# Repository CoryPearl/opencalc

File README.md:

<p align="center"><strong>Prototype sponsored by <a href="https://www.pcbway.com/">PCBWay</a>.</strong></p>

OpenCalc is an open-source graphing calculator inspired by the TI-84, built around an ESP32-S3, a color LCD, USB-C, Python-style scripting, games, and expandable firmware.

OpenCalc-authored software is licensed under **GPL-3.0-or-later**. Bundled components retain their original licenses; see [Third-Party Notices](THIRD_PARTY_NOTICES.md).

The calculator runs **OpenCalc OS**, the project’s open-source ESP32-S3 operating environment. OpenCalc OS includes the calculator interface, math and graphing engines, built-in apps, scripting runtime, USB file storage, keypad handling, display drivers, game support, and power management.

Website: [https://corypearl.github.io/opencalc/product-website/](https://corypearl.github.io/opencalc/product-website/)

Blog: [https://corypearl.github.io/opencalc/blog.html](https://corypearl.github.io/opencalc/blog.html)

<p align="center">

</p>
<p align="center"><small>Click an image to enlarge. The UI tour visits all 12 apps and the game menu.</small></p>

## Highlights

- **A real graphing calculator:** textbook-style input, exact and numerical
  math, complex numbers, calculus, history, typed persistent variables, and
  unit-aware expressions such as `8 m / 2 s`.
- **Integrated CAS and graphing:** Giac/KhiCAS symbolic math linked to Cartesian,
  parametric, polar, and sequence graphs, tables, roots, derivatives, tangents,
  integrals, and points of interest. `Alpha` + `Graph` opens exact symbolic
  analysis for the selected graph, including its derivative, integral, roots,
  asymptotes, tangent line, and integral shading. CAS results have selectable
  solution branches, exact/decimal views, domain controls, assumptions, and a
  searchable command catalog.
  All graph modes support per-series colors/styles, mode-aware trace and tables,
  scalable image backgrounds, and direct or recurrent sequences.
- **A complete math toolkit:** Statistics, Lists, Matrices, Solver, Finance,
  Conics, Inequalities, and a searchable science and engineering reference.
- **Reference Center:** press `Alpha` + `Zoom` for an interactive periodic table
  and browsable math, physics, and engineering formulas and explanations.
- **Programmable on the device:** edit, run, upload, and debug Tiny Python programs with
  math, statistics, exceptions, local modules, cancellable forever loops, CAS
  access, graphics, storage, audio, and protected CircuitPython-style sensor objects.
- **[Built for science and electronics](guied.MD#scientific-data-logging):** use Tiny Python,
  12 bidirectional digital pins, four 16-bit analog inputs, and shared I2C to
  control experiments, plot live sensor data, and analyze recordings in Stats.
- **Games included:** press `Alpha` + `2nd` for Tetris, Doom, Snake, Breakout, and NES/Mario support with
  persistent high scores, multi-key controls, and optional audio.
- **Open hardware:** ESP32-S3, 320x240 color display, diode-isolated keypad,
  rechargeable battery, USB-C, expandable storage, and a documented V5 PCB.
- **One-cable workflow:** the same USB-C connection handles charging, firmware
  flashing, serial monitoring, and file storage.
- **Dual-core OpenCalc OS:** one core keeps the interface and graphics responsive
  while the other handles background math and system work, with persistent
  worksheets, configurable performance, and power-saving controls.

## Rough production Cost Estimate

| Cost area                           | Estimate per unit |
| ----------------------------------- | ----------------- |
| PCB electronics parts from BOM      | $11-$16           |
| 320x240 LCD                         | $5                |
| 3.7 V 2000 mAh Li-ion battery       | $3-$5             |
| Cheap keycaps / keypad plastics     | $2-$4             |
| 3d printed case                     | $3-$6             |
| PCB fabrication + SMT assembly      | $5-$9             |
| Bulk shipping / logistics allowance | $3-$6             |
| Estimated production cost           | $32-$51           |

## Project Layout

```text
firmware/   OpenCalc OS source for the ESP32-S3 calculator
hardware/   key layouts, graphics, PCB files, case files, and hardware docs
docs/       notes and project website files
```

## Quick Start

Install and activate ESP-IDF first; see Espressif's
[ESP32-S3 Get Started guide](https://docs.espressif.com/projects/esp-idf/en/latest/esp32s3/get-started/).
Then connect OpenCalc with a data-capable USB-C cable and build the firmware:

```console
cd firmware
idf.py build
```

Find the serial port created by OpenCalc:

| System  | Terminal       | Command                                        |
| ------- | -------------- | ---------------------------------------------- |
| macOS   | Terminal       | `ls /dev/cu.*`                                 |
| Linux   | Terminal       | `ls /dev/ttyACM* /dev/ttyUSB* 2>/dev/null`     |
| Windows | PowerShell     | `[System.IO.Ports.SerialPort]::GetPortNames()` |
| Windows | Command Prompt | `mode`                                         |

Look for a new USB serial device after connecting the calculator. Typical names
are `/dev/cu.usbmodemopencalc1` on macOS, `/dev/ttyACM0` on Linux, or `COM5` on
Windows. Replace `PORT` below with that complete name; do not type the word
`PORT` literally.

If automatic flashing does not enter the bootloader, hold **Boot**, tap
**Reset**, and then release **Boot**. Flash using the detected port:

```text
idf.py -p PORT flash
```

After OpenCalc restarts, find the port again because its name can change between
bootloader and normal operation. Start the serial monitor with the runtime port:

```text
idf.py -p PORT monitor
```

Press `Ctrl+]` to exit the monitor. The same USB-C cable supports flashing,
serial monitoring, storage, and charging.

## Documentation

- [Complete OpenCalc OS Guide](guied.MD): in-depth controls, app workflows, games, scripting, settings, build instructions, validation, and troubleshooting.
- [Tiny Python Start Guide](TINY_PYTHON_START_GUIDE.md): create, run, and debug scripts; use imports, math, files, graphics, audio, keys, and scientific I/O.
- [Firmware README](firmware/FIRMWARE_README.md): build settings, flashing, storage image, controls, apps, games, and firmware status.
- [App Status](firmware/APP_STATUS.md): implementation status for every OpenCalc OS app and game.
- [PCB README](hardware/pcb/PCB_README.md): current V5 PCB parts, pin map, power path, display, keypad, battery, audio, and bring-up checks.
- [Tiny Python README](firmware/main/components/tiny-python-readme.md): scripting runtime details.
- [Tiny Python capability audit](firmware/TINY_PYTHON_AUDIT.md): supported Python and hardware APIs, limits, and the CircuitPython compatibility boundary.

## Current Status

OpenCalc OS is a capable working prototype. Every built-in app has its main
workflow in place, and the calculator, graphing, CAS, scripting, USB storage,
power controls, and all five games are usable. The remaining work is mostly
deeper edge-case handling, long-session reliability, and validation of the new
V5-only hardware features.

| Area | Current estimate |
| --- | ---: |
| Primary app workflows implemented | 12/12 (100%) |
| Automated host test groups passing | 19/19 (100%) |
| Planned software feature coverage | About 87% |
| Everyday workflow usability | About 83% |
| Software reliability confidence | About 75% |
| Production-release readiness | About 50% |

These percentages are practical estimates, not test-coverage measurements. The
biggest jobs left are closing Tiny Python's compatibility gaps, handling very
large CAS results and unusual math edge cases, stress-testing large matrices and
long sessions, and validating V5 audio and scientific I/O on real hardware. See the
[app-by-app status](firmware/APP_STATUS.md) for more detail.

## Credits

- OpenCalc OS, hardware, and enclosure design: [Cory Pearl](https://github.com/CoryPearl).
- CAS engines: [Giac/Xcas](https://xcas.univ-grenoble-alpes.fr/) by Bernard Parisse and contributors, with the [KhiCAS](https://github.com/KhiCAS) ESP32 port lineage under GPL-3.0-or-later; [Eigenmath](https://github.com/georgeweigt/eigenmath) remains as a BSD-2-Clause fallback.
- Doom engine: id Software's GPL Doom source, Simon Howard's Chocolate Doom work, and [doomgeneric](https://github.com/ozkl/doomgeneric) by ozkl, under GPL-2.0-or-later notices.
- NES emulation: [Anemoia-ESP32](https://github.com/Shim06/Anemoia-ESP32) by Shim06 and contributors, under GPLv3.
- Platform: [Espressif ESP-IDF](https://github.com/espressif/esp-idf), TinyUSB, and the ESP LCD ILI9341/ST7789 panel drivers under their respective licenses.
- Prototype project funding was provided in part by [PCBWay](https://pcbway.com).

Complete copyright, license, and game-data details are recorded in [THIRD_PARTY_NOTICES.md](THIRD_PARTY_NOTICES.md). Doom WADs and NES ROMs are separate game data and are not licensed under the OpenCalc firmware license.

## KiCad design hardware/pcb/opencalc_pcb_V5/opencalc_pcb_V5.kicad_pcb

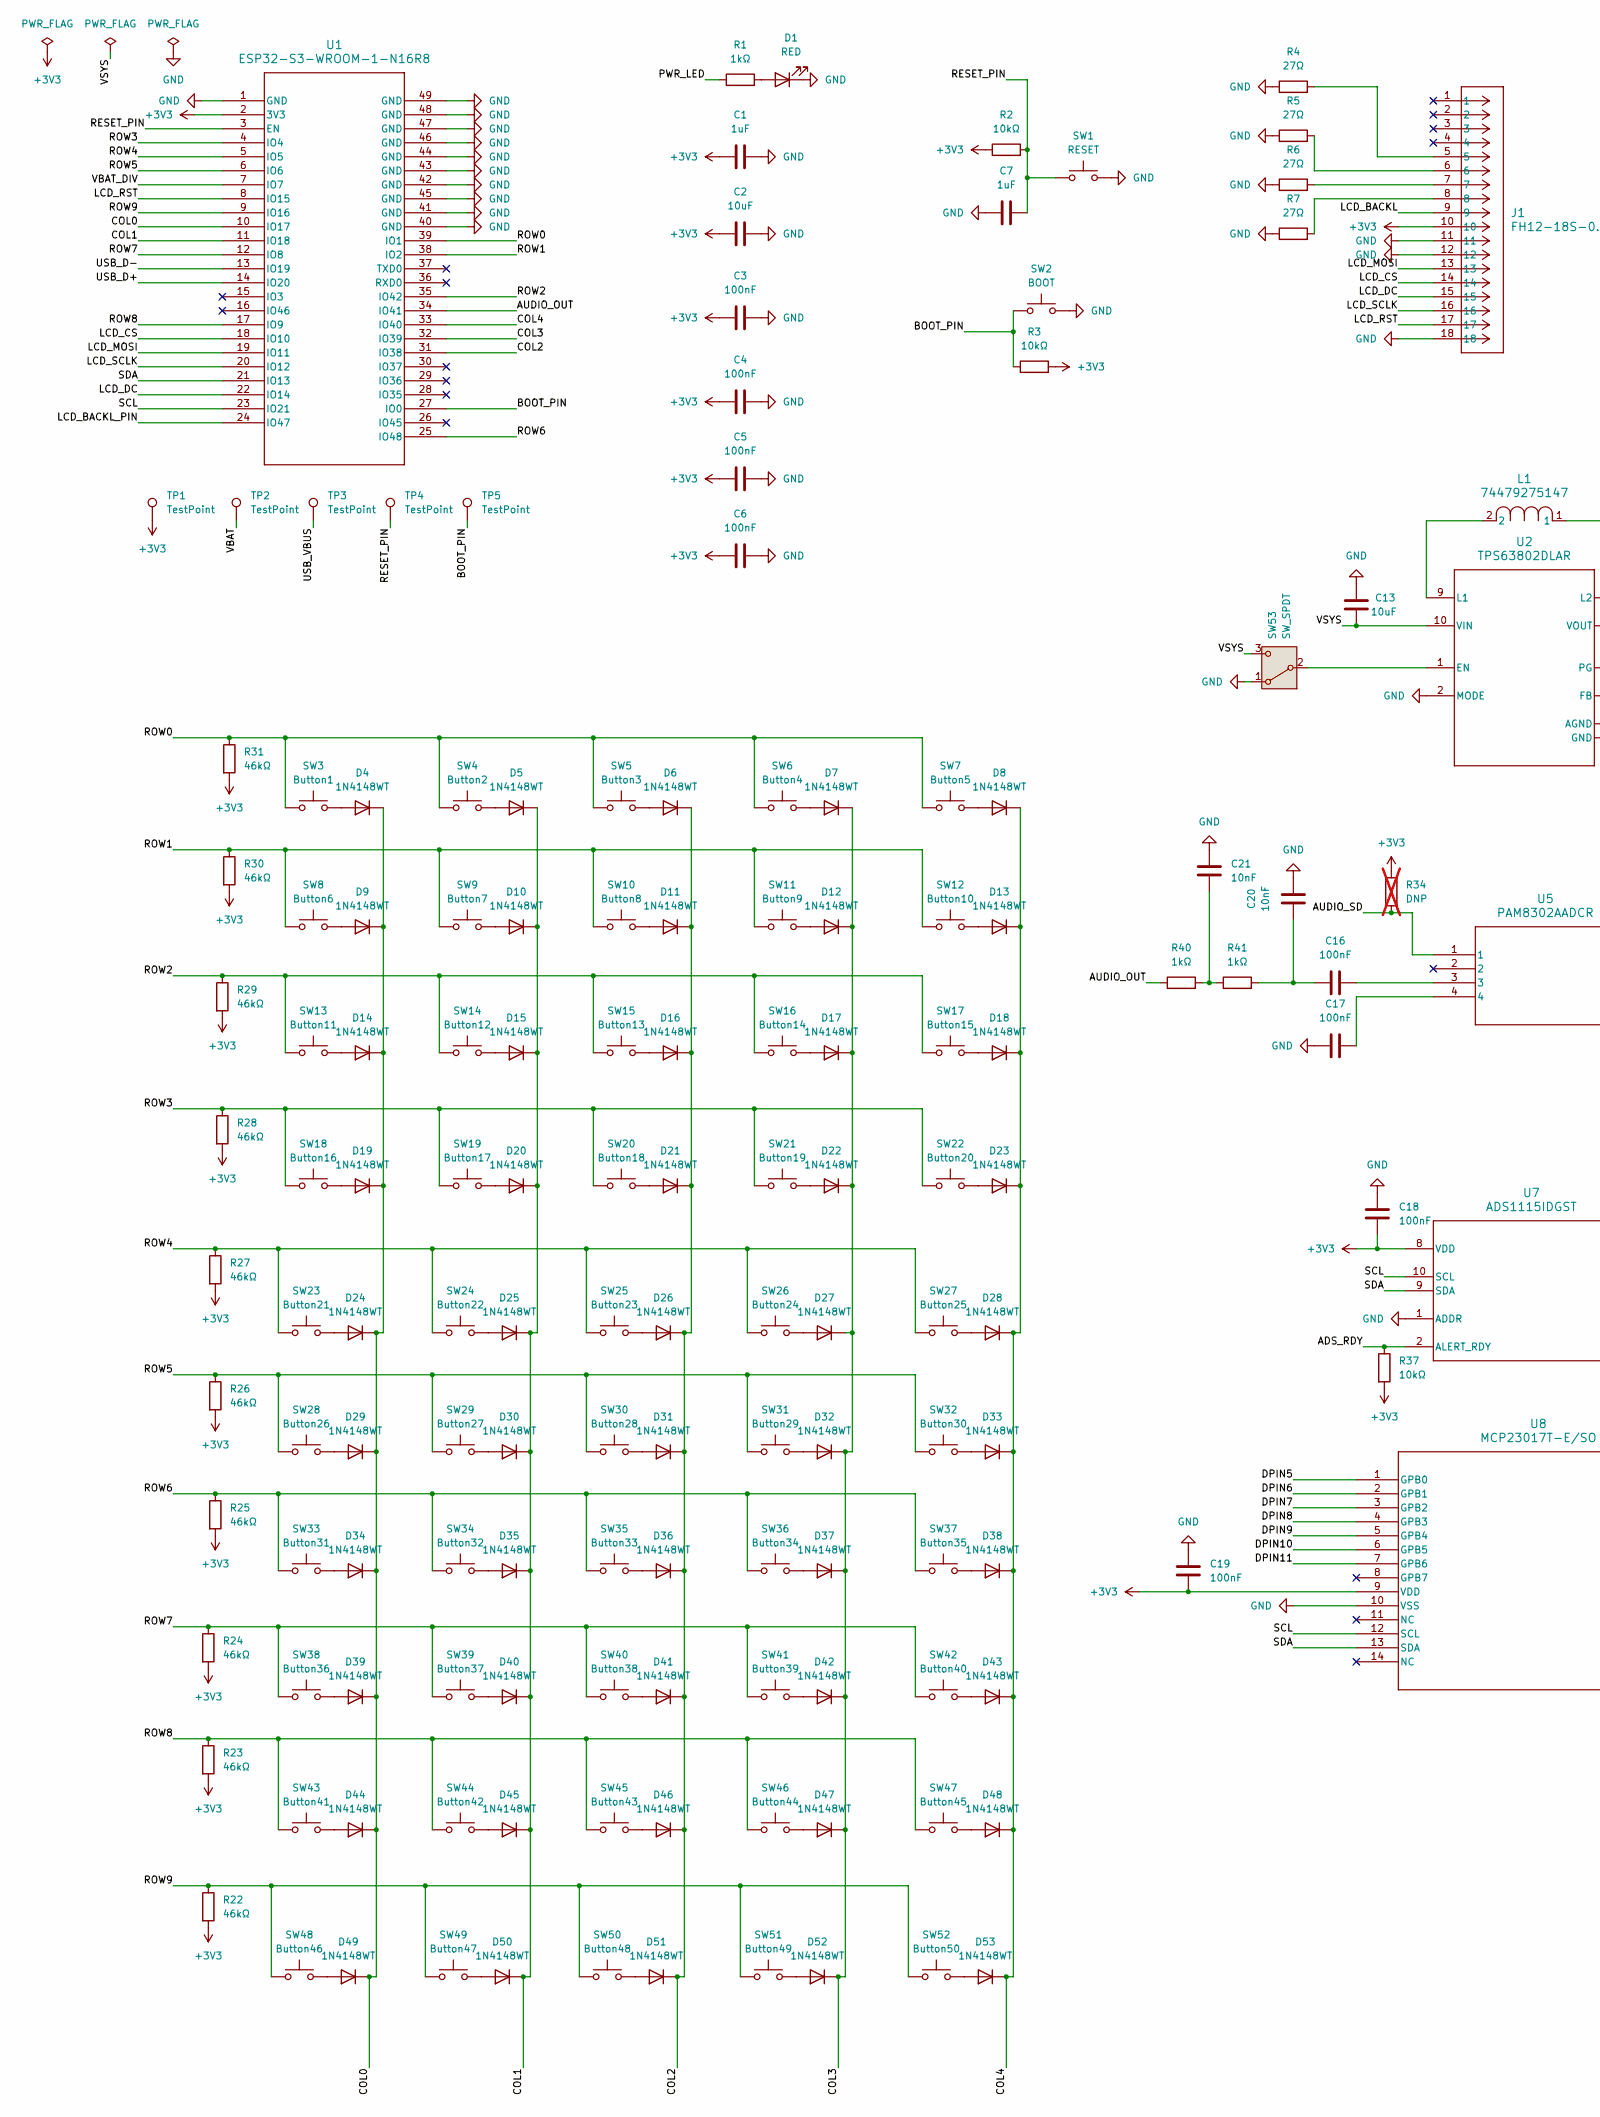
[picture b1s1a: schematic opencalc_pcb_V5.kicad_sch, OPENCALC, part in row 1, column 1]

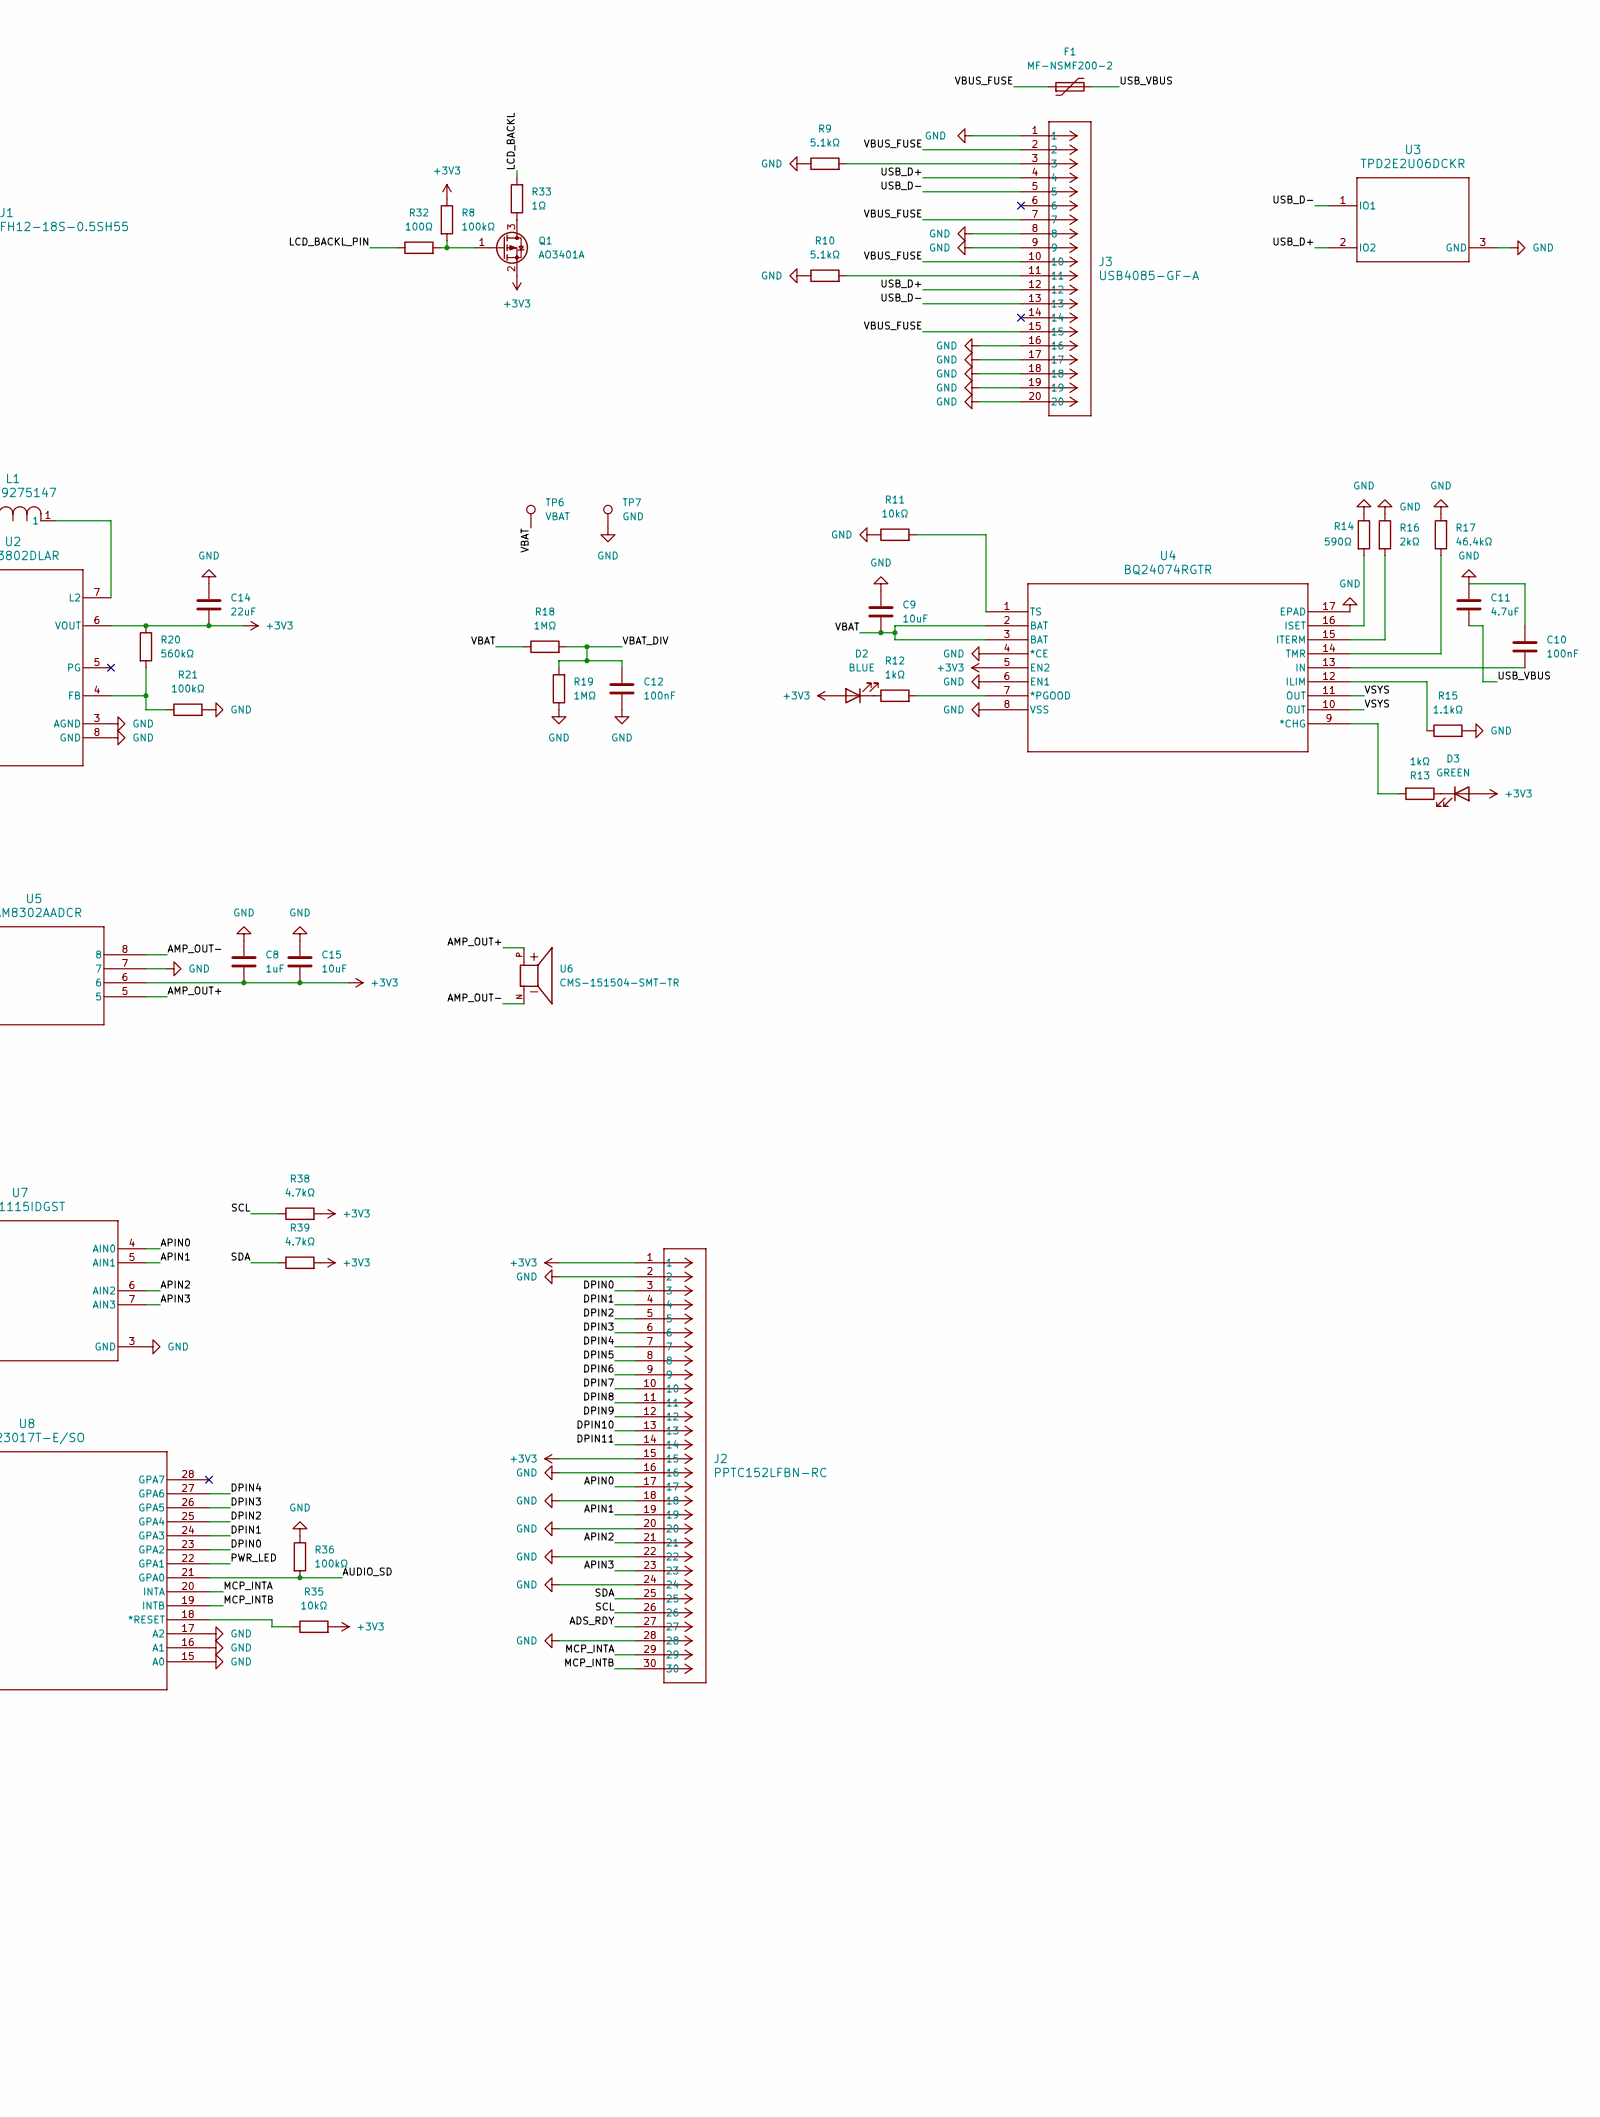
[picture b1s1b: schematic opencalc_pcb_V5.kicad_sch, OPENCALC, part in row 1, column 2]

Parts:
C1, C7, C8: 1uF; C_0805_2012Metric_Pad1.18x1.45mm_HandSolder
C2, C9, C13, C15: 10uF; C_0805_2012Metric_Pad1.18x1.45mm_HandSolder
C3, C4, C5, C6, C10, C12, C16, C17, C18, C19: 100nF; C_0805_2012Metric_Pad1.18x1.45mm_HandSolder
C11: 4.7uF; C_0805_2012Metric_Pad1.18x1.45mm_HandSolder
C14: 22uF; C_0805_2012Metric_Pad1.18x1.45mm_HandSolder
C20, C21: 10nF; C_0805_2012Metric_Pad1.18x1.45mm_HandSolder
D1: RED; LED_0805_2012Metric_Pad1.15x1.40mm_HandSolder
D2: BLUE; LED_0805_2012Metric_Pad1.15x1.40mm_HandSolder
D3: GREEN; LED_0805_2012Metric_Pad1.15x1.40mm_HandSolder
D4, D5, D6, D7, D8, D9, D10, D11, D12, D13, D14, D15, D16, D17, D18, D19, D20, D21, D22, D23, D24, D25, D26, D27, D28, D29, D30, D31, D32, D33, D34, D35, D36, D37, D38, D39, D40, D41, D42, D43, D44, D45, D46, D47, D48, D49, D50, D51, D52, D53: 1N4148WT; D_0805_2012Metric_Pad1.15x1.40mm_HandSolder
F1: MF-NSMF200-2; Fuse_1206_3216Metric
J1: FH12-18S-0.5SH55; FH12-18S-0.5SH(55)
J2: PPTC152LFBN-RC; PPTC152LFBN_RC
J3: USB4085-GF-A
L1: 74479275147
Q1: AO3401A; SOT-23
R1, R12, R13, R40, R41: 1kΩ; R_0805_2012Metric_Pad1.20x1.40mm_HandSolder
R2, R3, R11, R35, R37: 10kΩ; R_0805_2012Metric_Pad1.20x1.40mm_HandSolder
R4, R5, R6, R7: 27Ω; R_0805_2012Metric_Pad1.20x1.40mm_HandSolder
R8, R21, R36: 100kΩ; R_0805_2012Metric_Pad1.20x1.40mm_HandSolder
R9, R10: 5.1kΩ; R_0805_2012Metric_Pad1.20x1.40mm_HandSolder
R14: 590Ω; R_0805_2012Metric_Pad1.20x1.40mm_HandSolder
R15: 1.1kΩ; R_0805_2012Metric_Pad1.20x1.40mm_HandSolder
R16: 2kΩ; R_0805_2012Metric_Pad1.20x1.40mm_HandSolder
R17: 46.4kΩ; R_0805_2012Metric_Pad1.20x1.40mm_HandSolder
R18, R19: 1MΩ; R_0805_2012Metric_Pad1.20x1.40mm_HandSolder
R20: 560kΩ; R_0805_2012Metric_Pad1.20x1.40mm_HandSolder
R22, R23, R24, R25, R26, R27, R28, R29, R30, R31: 46kΩ; R_0805_2012Metric_Pad1.20x1.40mm_HandSolder
R32: 100Ω; R_0805_2012Metric_Pad1.20x1.40mm_HandSolder
R33: 1Ω; R_0805_2012Metric_Pad1.20x1.40mm_HandSolder
R34: DNP; R_0805_2012Metric_Pad1.20x1.40mm_HandSolder; not fitted
R38, R39: 4.7kΩ; R_0805_2012Metric_Pad1.20x1.40mm_HandSolder
SW1: RESET; SW_Push_1P1T_NO_E-Switch_TL3301NxxxxxG
SW2: BOOT; SW_Push_1P1T_NO_E-Switch_TL3301NxxxxxG
SW3: Button1; SW_Push_1P1T_NO_E-Switch_TL3301NxxxxxG
SW4: Button2; SW_Push_1P1T_NO_E-Switch_TL3301NxxxxxG
SW5: Button3; SW_Push_1P1T_NO_E-Switch_TL3301NxxxxxG
SW6: Button4; SW_Push_1P1T_NO_E-Switch_TL3301NxxxxxG
SW7: Button5; SW_Push_1P1T_NO_E-Switch_TL3301NxxxxxG
SW8: Button6; SW_Push_1P1T_NO_E-Switch_TL3301NxxxxxG
SW9: Button7; SW_Push_1P1T_NO_E-Switch_TL3301NxxxxxG
SW10: Button8; SW_Push_1P1T_NO_E-Switch_TL3301NxxxxxG
SW11: Button9; SW_Push_1P1T_NO_E-Switch_TL3301NxxxxxG
SW12: Button10; SW_Push_1P1T_NO_E-Switch_TL3301NxxxxxG
SW13: Button11; SW_Push_1P1T_NO_E-Switch_TL3301NxxxxxG
SW14: Button12; SW_Push_1P1T_NO_E-Switch_TL3301NxxxxxG
SW15: Button13; SW_Push_1P1T_NO_E-Switch_TL3301NxxxxxG
SW16: Button14; SW_Push_1P1T_NO_E-Switch_TL3301NxxxxxG
SW17: Button15; SW_Push_1P1T_NO_E-Switch_TL3301NxxxxxG
SW18: Button16; SW_Push_1P1T_NO_E-Switch_TL3301NxxxxxG
SW19: Button17; SW_Push_1P1T_NO_E-Switch_TL3301NxxxxxG
SW20: Button18; SW_Push_1P1T_NO_E-Switch_TL3301NxxxxxG
SW21: Button19; SW_Push_1P1T_NO_E-Switch_TL3301NxxxxxG
SW22: Button20; SW_Push_1P1T_NO_E-Switch_TL3301NxxxxxG
SW23: Button21; SW_Push_1P1T_NO_E-Switch_TL3301NxxxxxG
SW24: Button22; SW_Push_1P1T_NO_E-Switch_TL3301NxxxxxG
SW25: Button23; SW_Push_1P1T_NO_E-Switch_TL3301NxxxxxG
SW26: Button24; SW_Push_1P1T_NO_E-Switch_TL3301NxxxxxG
SW27: Button25; SW_Push_1P1T_NO_E-Switch_TL3301NxxxxxG
SW28: Button26; SW_Push_1P1T_NO_E-Switch_TL3301NxxxxxG
SW29: Button27; SW_Push_1P1T_NO_E-Switch_TL3301NxxxxxG
SW30: Button28; SW_Push_1P1T_NO_E-Switch_TL3301NxxxxxG
SW31: Button29; SW_Push_1P1T_NO_E-Switch_TL3301NxxxxxG
SW32: Button30; SW_Push_1P1T_NO_E-Switch_TL3301NxxxxxG
SW33: Button31; SW_Push_1P1T_NO_E-Switch_TL3301NxxxxxG
SW34: Button32; SW_Push_1P1T_NO_E-Switch_TL3301NxxxxxG
SW35: Button33; SW_Push_1P1T_NO_E-Switch_TL3301NxxxxxG
SW36: Button34; SW_Push_1P1T_NO_E-Switch_TL3301NxxxxxG
SW37: Button35; SW_Push_1P1T_NO_E-Switch_TL3301NxxxxxG
SW38: Button36; SW_Push_1P1T_NO_E-Switch_TL3301NxxxxxG
SW39: Button37; SW_Push_1P1T_NO_E-Switch_TL3301NxxxxxG
SW40: Button38; SW_Push_1P1T_NO_E-Switch_TL3301NxxxxxG
SW41: Button39; SW_Push_1P1T_NO_E-Switch_TL3301NxxxxxG
SW42: Button40; SW_Push_1P1T_NO_E-Switch_TL3301NxxxxxG
SW43: Button41; SW_Push_1P1T_NO_E-Switch_TL3301NxxxxxG
SW44: Button42; SW_Push_1P1T_NO_E-Switch_TL3301NxxxxxG
SW45: Button43; SW_Push_1P1T_NO_E-Switch_TL3301NxxxxxG
SW46: Button44; SW_Push_1P1T_NO_E-Switch_TL3301NxxxxxG
SW47: Button45; SW_Push_1P1T_NO_E-Switch_TL3301NxxxxxG
SW48: Button46; SW_Push_1P1T_NO_E-Switch_TL3301NxxxxxG
SW49: Button47; SW_Push_1P1T_NO_E-Switch_TL3301NxxxxxG
SW50: Button48; SW_Push_1P1T_NO_E-Switch_TL3301NxxxxxG
SW51: Button49; SW_Push_1P1T_NO_E-Switch_TL3301NxxxxxG
SW52: Button50; SW_Push_1P1T_NO_E-Switch_TL3301NxxxxxG
SW53: SW_SPDT; SW_SPDT_CK_JS102011SAQN
TP1, TP2, TP3, TP4, TP5: TestPoint; TestPoint_Pad_D2.0mm
TP6: VBAT; TestPoint_THTPad_3.0x3.0mm_Drill1.5mm
TP7: GND; TestPoint_THTPad_3.0x3.0mm_Drill1.5mm
U1: ESP32-S3-WROOM-1-N16R8; ESP32-S3-WROOM-1
U2: TPS63802DLAR
U3: TPD2E2U06DCKR
U4: BQ24074RGTR
U5: PAM8302AADCR
U6: CMS-151504-SMT-TR; PARTREV 1.02
U7: ADS1115IDGST
U8: MCP23017T-E/SO; MCP23017T_E_SO

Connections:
+3V3: C1.1, C2.1, C3.1, C4.1, C5.1, C6.1, C8.2, C14.1, C15.2, C18.2, C19.2, D2.2 (A), D3.2 (A), J1.10, J2.1, J2.15, Q1.2 (S), R2.1, R3.2, R8.1, R20.1, R22.2, R23.2, R24.2, R25.2, R26.2, R27.2, R28.2, R29.2, R30.2, R31.2, R34.1, R35.2, R37.2, R38.2, R39.2, TP1.1, U1.2 (3V3), U2.6 (VOUT), U4.5 (EN2), U5.6, U7.8 (VDD), U8.9 (VDD)
/ADS_RDY: J2.27, R37.1, U7.2 (ALERT_RDY)
/AMP_OUT+: U5.5, U6.P
/AMP_OUT-: U5.8, U6.N
/APIN0: J2.17, U7.4 (AIN0)
/APIN1: J2.19, U7.5 (AIN1)
/APIN2: J2.21, U7.6 (AIN2)
/APIN3: J2.23, U7.7 (AIN3)
/AUDIO_OUT: R40.1, U1.34 (IO41)
/AUDIO_SD: R34.2, R36.2, U5.1, U8.21 (GPA0)
/BOOT_PIN: R3.1, SW2.1, TP5.1, U1.27 (IO0)
/COL0: D4.1 (K), D9.1 (K), D14.1 (K), D19.1 (K), D24.1 (K), D29.1 (K), D34.1 (K), D39.1 (K), D44.1 (K), D49.1 (K), U1.10 (IO17)
/COL1: D5.1 (K), D10.1 (K), D15.1 (K), D20.1 (K), D25.1 (K), D30.1 (K), D35.1 (K), D40.1 (K), D45.1 (K), D50.1 (K), U1.11 (IO18)
/COL2: D6.1 (K), D11.1 (K), D16.1 (K), D21.1 (K), D26.1 (K), D31.1 (K), D36.1 (K), D41.1 (K), D46.1 (K), D51.1 (K), U1.31 (IO38)
/COL3: D7.1 (K), D12.1 (K), D17.1 (K), D22.1 (K), D27.1 (K), D32.1 (K), D37.1 (K), D42.1 (K), D47.1 (K), D52.1 (K), U1.32 (IO39)
/COL4: D8.1 (K), D13.1 (K), D18.1 (K), D23.1 (K), D28.1 (K), D33.1 (K), D38.1 (K), D43.1 (K), D48.1 (K), D53.1 (K), U1.33 (IO40)
/DPIN0: J2.3, U8.23 (GPA2)
/DPIN1: J2.4, U8.24 (GPA3)
/DPIN2: J2.5, U8.25 (GPA4)
/DPIN3: J2.6, U8.26 (GPA5)
/DPIN4: J2.7, U8.27 (GPA6)
/DPIN5: J2.8, U8.1 (GPB0)
/DPIN6: J2.9, U8.2 (GPB1)
/DPIN7: J2.10, U8.3 (GPB2)
/DPIN8: J2.11, U8.4 (GPB3)
/DPIN9: J2.12, U8.5 (GPB4)
/DPIN10: J2.13, U8.6 (GPB5)
/DPIN11: J2.14, U8.7 (GPB6)
/LCD_BACKL: J1.9, R33.2
/LCD_BACKL_PIN: R32.1, U1.24 (IO47)
/LCD_CS: J1.14, U1.18 (IO10)
/LCD_DC: J1.15, U1.22 (IO14)
/LCD_MOSI: J1.13, U1.19 (IO11)
/LCD_RST: J1.17, U1.8 (IO15)
/LCD_SCLK: J1.16, U1.20 (IO12)
/MCP_INTA: J2.29, U8.20 (INTA)
/MCP_INTB: J2.30, U8.19 (INTB)
/PWR_LED: R1.1, U8.22 (GPA1)
/RESET_PIN: C7.2, R2.2, SW1.1, TP4.1, U1.3 (EN)
/ROW0: R31.1, SW3.1, SW4.1, SW5.1, SW6.1, SW7.1, U1.39 (IO1)
/ROW1: R30.1, SW8.1, SW9.1, SW10.1, SW11.1, SW12.1, U1.38 (IO2)
/ROW2: R29.1, SW13.1, SW14.1, SW15.1, SW16.1, SW17.1, U1.35 (IO42)
/ROW3: R28.1, SW18.1, SW19.1, SW20.1, SW21.1, SW22.1, U1.4 (IO4)
/ROW4: R27.1, SW23.1, SW24.1, SW25.1, SW26.1, SW27.1, U1.5 (IO5)
/ROW5: R26.1, SW28.1, SW29.1, SW30.1, SW31.1, SW32.1, U1.6 (IO6)
/ROW6: R25.1, SW33.1, SW34.1, SW35.1, SW36.1, SW37.1, U1.25 (IO48)
/ROW7: R24.1, SW38.1, SW39.1, SW40.1, SW41.1, SW42.1, U1.12 (IO8)
/ROW8: R23.1, SW43.1, SW44.1, SW45.1, SW46.1, SW47.1, U1.17 (IO9)
/ROW9: R22.1, SW48.1, SW49.1, SW50.1, SW51.1, SW52.1, U1.9 (IO16)
/SCL: J2.26, R38.1, U1.23 (IO21), U7.10 (SCL), U8.12 (SCL)
/SDA: J2.25, R39.1, U1.21 (IO13), U7.9 (SDA), U8.13 (SDA)
/USB_D+: J3.4, J3.12, U1.14 (IO20), U3.2 (IO2)
/USB_D-: J3.5, J3.13, U1.13 (IO19), U3.1 (IO1)
/USB_VBUS: C10.2, C11.2, F1.2, TP3.1, U4.13 (IN)
/VBAT: C9.1, R18.1, TP2.1, TP6.1, U4.2 (BAT), U4.3 (BAT)
/VBAT_DIV: C12.1, R18.2, R19.2, U1.7 (IO7)
/VBUS_FUSE: F1.1, J3.2, J3.7, J3.10, J3.15
/VSYS: C13.2, SW53.3 (C), U2.10 (VIN), U4.10 (OUT), U4.11 (OUT)
GND: C1.2, C2.2, C3.2, C4.2, C5.2, C6.2, C7.1, C8.1, C9.2, C10.1, C11.1, C12.2, C13.1, C14.2, C15.1, C17.1, C18.1, C19.1, C20.2, C21.2, D1.1 (K), J1.11, J1.12, J1.18, J2.2, J2.16, J2.18, J2.20, J2.22, J2.24, J2.28, J3.1, J3.8, J3.9, J3.16, J3.17, J3.18, J3.19, J3.20, R4.1, R5.1, R6.1, R7.1, R9.1, R10.1, R11.1, R14.1, R15.2, R16.1, R17.2, R19.1, R21.2, R36.1, SW1.2, SW2.2, SW53.1 (A), TP7.1, U1.1 (GND), U1.40 (GND), U1.41 (GND), U1.42 (GND), U1.43 (GND), U1.44 (GND), U1.45 (GND), U1.46 (GND), U1.47 (GND), U1.48 (GND), U1.49 (GND), U2.2 (MODE), U2.3 (AGND), U2.8 (GND), U3.3 (GND), U4.4 (*CE), U4.6 (EN1), U4.8 (VSS), U4.17 (EPAD), U4.V, U5.7, U7.1 (ADDR), U7.3 (GND), U8.10 (VSS), U8.15 (A0), U8.16 (A1), U8.17 (A2)
unnamed: C16.1, C20.1, R41.2
unnamed: C16.2, U5.3
unnamed: C17.2, U5.4
unnamed: C21.1, R40.2, R41.1
unnamed: D1.2 (A), R1.2
unnamed: D2.1 (K), R12.1
unnamed: D3.1 (K), R13.1
unnamed: D4.2 (A), SW3.2
unnamed: D5.2 (A), SW4.2
unnamed: D6.2 (A), SW5.2
unnamed: D7.2 (A), SW6.2
unnamed: D8.2 (A), SW7.2
unnamed: D9.2 (A), SW8.2
unnamed: D10.2 (A), SW9.2
unnamed: D11.2 (A), SW10.2
unnamed: D12.2 (A), SW11.2
unnamed: D13.2 (A), SW12.2
unnamed: D14.2 (A), SW13.2
unnamed: D15.2 (A), SW14.2
unnamed: D16.2 (A), SW15.2
unnamed: D17.2 (A), SW16.2
unnamed: D18.2 (A), SW17.2
unnamed: D19.2 (A), SW18.2
unnamed: D20.2 (A), SW19.2
unnamed: D21.2 (A), SW20.2
unnamed: D22.2 (A), SW21.2
unnamed: D23.2 (A), SW22.2
unnamed: D24.2 (A), SW23.2
unnamed: D25.2 (A), SW24.2
unnamed: D26.2 (A), SW25.2
unnamed: D27.2 (A), SW26.2
unnamed: D28.2 (A), SW27.2
unnamed: D29.2 (A), SW28.2
unnamed: D30.2 (A), SW29.2
unnamed: D31.2 (A), SW30.2
unnamed: D32.2 (A), SW31.2
unnamed: D33.2 (A), SW32.2
unnamed: D34.2 (A), SW33.2
unnamed: D35.2 (A), SW34.2
unnamed: D36.2 (A), SW35.2
unnamed: D37.2 (A), SW36.2
unnamed: D38.2 (A), SW37.2
unnamed: D39.2 (A), SW38.2
unnamed: D40.2 (A), SW39.2
unnamed: D41.2 (A), SW40.2
unnamed: D42.2 (A), SW41.2
unnamed: D43.2 (A), SW42.2
unnamed: D44.2 (A), SW43.2
unnamed: D45.2 (A), SW44.2
unnamed: D46.2 (A), SW45.2
unnamed: D47.2 (A), SW46.2
unnamed: D48.2 (A), SW47.2
unnamed: D49.2 (A), SW48.2
unnamed: D50.2 (A), SW49.2
unnamed: D51.2 (A), SW50.2
unnamed: D52.2 (A), SW51.2
unnamed: D53.2 (A), SW52.2
unnamed: J1.5, R4.2
unnamed: J1.6, R5.2
unnamed: J1.7, R6.2
unnamed: J1.8, R7.2
unnamed: J3.3, R9.2
unnamed: J3.11, R10.2
unnamed: Q1.3 (D), R33.1
unnamed: Q1.1 (G), R8.2, R32.2
unnamed: SW53.2 (B), U2.1 (EN)
unnamed: R20.2, R21.1, U2.4 (FB)
unnamed: L1.2, U2.9 (L1)
unnamed: L1.1, U2.7 (L2)
unnamed: R13.2, U4.9 (*CHG)
unnamed: R12.2, U4.7 (*PGOOD)
unnamed: R15.1, U4.12 (ILIM)
unnamed: R14.2, U4.16 (ISET)
unnamed: R16.2, U4.15 (ITERM)
unnamed: R17.1, U4.14 (TMR)
unnamed: R11.2, U4.1 (TS)
unnamed: R35.1, U8.18 (*RESET)

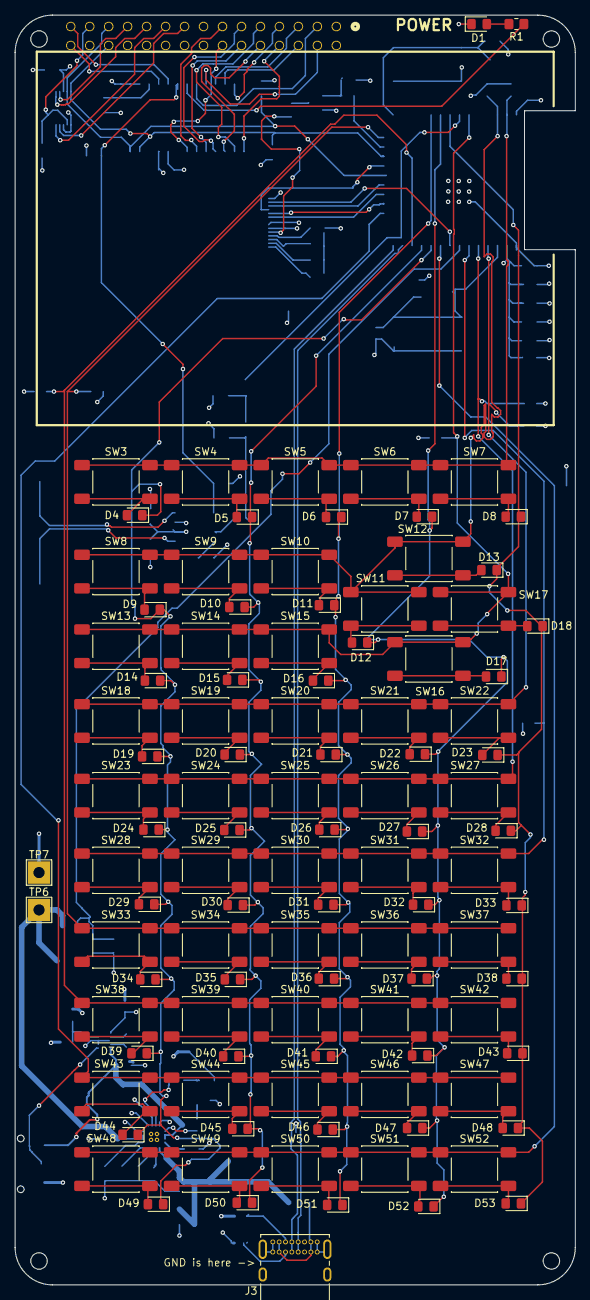
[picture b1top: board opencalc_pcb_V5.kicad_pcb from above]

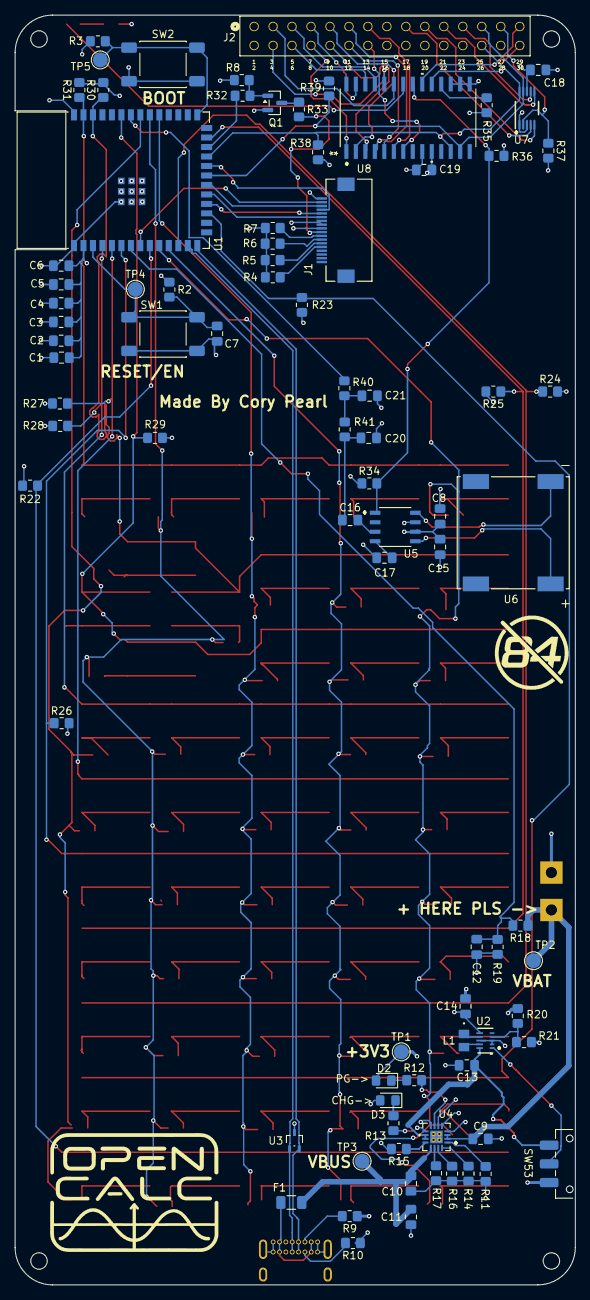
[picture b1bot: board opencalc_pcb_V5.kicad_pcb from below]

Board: 4 copper layers, 75.0 x 170.0 mm, 189 parts (84 on the bottom side), 136 nets.

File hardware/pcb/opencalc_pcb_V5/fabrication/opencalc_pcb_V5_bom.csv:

Id,Designator,Footprint,Quantity,Designation,Supplier and ref,,
1,"D40,D38,D15,D48,D24,D26,D14,D50,D52,D34,D39,D18,D22,D4,D33,D47,D5,D29,D19,D49,D37,D10,D23,D25,D51,D32,D53,D20,D31,D11,D30,D43,D45,D8,D36,D27,D9,D41,D42,D44,D17,D21,D7,D35,D46,D13,D12,D16,D28,D6",D_SOD-523,50,1N4148WT,,,
2,SW31,SW_Push_1P1T_NO_E-Switch_TL3301NxxxxxG,1,Button29,,,
3,SW37,SW_Push_1P1T_NO_E-Switch_TL3301NxxxxxG,1,Button35,,,
4,SW27,SW_Push_1P1T_NO_E-Switch_TL3301NxxxxxG,1,Button25,,,
5,SW35,SW_Push_1P1T_NO_E-Switch_TL3301NxxxxxG,1,Button33,,,
6,SW36,SW_Push_1P1T_NO_E-Switch_TL3301NxxxxxG,1,Button34,,,
7,SW19,SW_Push_1P1T_NO_E-Switch_TL3301NxxxxxG,1,Button17,,,
8,SW24,SW_Push_1P1T_NO_E-Switch_TL3301NxxxxxG,1,Button22,,,
9,SW46,SW_Push_1P1T_NO_E-Switch_TL3301NxxxxxG,1,Button44,,,
10,SW30,SW_Push_1P1T_NO_E-Switch_TL3301NxxxxxG,1,Button28,,,
11,J3,USB4085-GF-A,1,USB4085-GF-A,,,
12,SW38,SW_Push_1P1T_NO_E-Switch_TL3301NxxxxxG,1,Button36,,,
13,SW26,SW_Push_1P1T_NO_E-Switch_TL3301NxxxxxG,1,Button24,,,
14,"R1,R12,R13",R_0603_1608Metric,3,1kΩ,,,
15,SW4,SW_Push_1P1T_NO_E-Switch_TL3301NxxxxxG,1,Button2,,,
16,SW51,SW_Push_1P1T_NO_E-Switch_TL3301NxxxxxG,1,Button49,,,
17,SW20,SW_Push_1P1T_NO_E-Switch_TL3301NxxxxxG,1,Button18,,,
18,SW17,SW_Push_1P1T_NO_E-Switch_TL3301NxxxxxG,1,Button15,,,
19,SW18,SW_Push_1P1T_NO_E-Switch_TL3301NxxxxxG,1,Button16,,,
20,SW22,SW_Push_1P1T_NO_E-Switch_TL3301NxxxxxG,1,Button20,,,
21,SW23,SW_Push_1P1T_NO_E-Switch_TL3301NxxxxxG,1,Button21,,,
22,SW10,SW_Push_1P1T_NO_E-Switch_TL3301NxxxxxG,1,Button8,,,
23,SW7,SW_Push_1P1T_NO_E-Switch_TL3301NxxxxxG,1,Button5,,,
24,TP7,TestPoint_THTPad_3.0x3.0mm_Drill1.5mm,1,GND,,,
25,SW41,SW_Push_1P1T_NO_E-Switch_TL3301NxxxxxG,1,Button39,,,
26,SW42,SW_Push_1P1T_NO_E-Switch_TL3301NxxxxxG,1,Button40,,,
27,SW29,SW_Push_1P1T_NO_E-Switch_TL3301NxxxxxG,1,Button27,,,
28,SW52,SW_Push_1P1T_NO_E-Switch_TL3301NxxxxxG,1,Button50,,,
29,SW15,SW_Push_1P1T_NO_E-Switch_TL3301NxxxxxG,1,Button13,,,
30,SW6,SW_Push_1P1T_NO_E-Switch_TL3301NxxxxxG,1,Button4,,,
31,SW50,SW_Push_1P1T_NO_E-Switch_TL3301NxxxxxG,1,Button48,,,
32,SW49,SW_Push_1P1T_NO_E-Switch_TL3301NxxxxxG,1,Button47,,,
33,SW25,SW_Push_1P1T_NO_E-Switch_TL3301NxxxxxG,1,Button23,,,
34,SW45,SW_Push_1P1T_NO_E-Switch_TL3301NxxxxxG,1,Button43,,,
35,SW43,SW_Push_1P1T_NO_E-Switch_TL3301NxxxxxG,1,Button41,,,
36,SW5,SW_Push_1P1T_NO_E-Switch_TL3301NxxxxxG,1,Button3,,,
37,SW40,SW_Push_1P1T_NO_E-Switch_TL3301NxxxxxG,1,Button38,,,
38,SW16,SW_Push_1P1T_NO_E-Switch_TL3301NxxxxxG,1,Button14,,,
39,SW44,SW_Push_1P1T_NO_E-Switch_TL3301NxxxxxG,1,Button42,,,
41,SW48,SW_Push_1P1T_NO_E-Switch_TL3301NxxxxxG,1,Button46,,,
42,SW14,SW_Push_1P1T_NO_E-Switch_TL3301NxxxxxG,1,Button12,,,
43,SW3,SW_Push_1P1T_NO_E-Switch_TL3301NxxxxxG,1,Button1,,,
44,D1,LED_0603_1608Metric,1,RED,,,
45,SW33,SW_Push_1P1T_NO_E-Switch_TL3301NxxxxxG,1,Button31,,,
46,SW8,SW_Push_1P1T_NO_E-Switch_TL3301NxxxxxG,1,Button6,,,
47,SW9,SW_Push_1P1T_NO_E-Switch_TL3301NxxxxxG,1,Button7,,,
48,SW11,SW_Push_1P1T_NO_E-Switch_TL3301NxxxxxG,1,Button9,,,
49,SW32,SW_Push_1P1T_NO_E-Switch_TL3301NxxxxxG,1,Button30,,,
50,SW28,SW_Push_1P1T_NO_E-Switch_TL3301NxxxxxG,1,Button26,,,
51,SW21,SW_Push_1P1T_NO_E-Switch_TL3301NxxxxxG,1,Button19,,,
52,SW13,SW_Push_1P1T_NO_E-Switch_TL3301NxxxxxG,1,Button11,,,
53,SW34,SW_Push_1P1T_NO_E-Switch_TL3301NxxxxxG,1,Button32,,,
54,SW39,SW_Push_1P1T_NO_E-Switch_TL3301NxxxxxG,1,Button37,,,
55,TP6,TestPoint_THTPad_3.0x3.0mm_Drill1.5mm,1,VBAT,,,
56,SW12,SW_Push_1P1T_NO_E-Switch_TL3301NxxxxxG,1,Button10,,,
57,SW47,SW_Push_1P1T_NO_E-Switch_TL3301NxxxxxG,1,Button45,,,
58,U2,TPS63802DLAR,1,TPS63802DLAR,,,
59,"C10,C12,C6,C16,C3,C4,C5,C17",C_0603_1608Metric,8,100nF,,,
60,R34,R_0603_1608Metric,1,10k,,,
61,"R31,R22,R27,R29,R28,R24,R23,R25,R26,R30",R_0603_1608Metric,10,46kΩ,,,
62,SW53,SW_SPDT_CK_JS102011SAQN,1,SW_SPDT,,,
63,"TP4,TP5,TP3,TP2,TP1",TestPoint_Pad_D2.0mm,5,TestPoint,,,
64,R15,R_0603_1608Metric,1,1.1kΩ,,,
65,"R5,R4,R7,R6",R_0603_1608Metric,4,27Ω,,,
66,L1,74479275147,1,74479275147,,,
67,R20,R_0603_1608Metric,1,560kΩ,,,
68,"R9,R10",R_0603_1608Metric,2,5.1kΩ,,,
69,"R19,R18",R_0603_1608Metric,2,1MΩ,,,
70,"R8,R21",R_0603_1608Metric,2,100kΩ,,,
71,SW1,SW_Push_1P1T_NO_E-Switch_TL3301NxxxxxG,1,RESET,,,
72,U3,TPD2E2U06DCKR,1,TPD2E2U06DCKR,,,
73,R14,R_0603_1608Metric,1,590Ω,,,
74,"R11,R2,R3",R_0603_1608Metric,3,10kΩ,,,
75,Q1,SOT-23,1,AO3401A,,,
76,D3,LED_0603_1608Metric,1,GREEN,,,
77,"C9,C2,C13,C15",C_0603_1608Metric,4,10uF,,,
78,F1,Fuse_1206_3216Metric,1,MF-NSMF200-2,,,
79,R17,R_0603_1608Metric,1,46.4kΩ,,,
80,"C1,C7,C8",C_0603_1608Metric,3,1uF,,,
81,U5,PAM8302AADCR,1,PAM8302AADCR,,,
82,C11,C_0603_1608Metric,1,4.7uF,,,
83,R32,R_0603_1608Metric,1,100Ω,,,
84,U1,ESP32-S3-WROOM-1,1,ESP32-S3-WROOM-1-N16R8,,,
85,R16,R_0603_1608Metric,1,4.4kΩ,,,
86,SW2,SW_Push_1P1T_NO_E-Switch_TL3301NxxxxxG,1,BOOT,,,
87,D2,LED_0603_1608Metric,1,BLUE,,,
88,J1,FH12-18S-0.5SH(55),1,FH12-18S-0.5SH55,,,
89,C14,C_0603_1608Metric,1,22uF,,,
90,U6,CMS-151504-SMT-TR,1,CMS-151504-SMT-TR,,,
91,U4,BQ24074RGTR,1,BQ24074RGTR,,,
92,R33,R_0603_1608Metric,1,33Ω,,,
